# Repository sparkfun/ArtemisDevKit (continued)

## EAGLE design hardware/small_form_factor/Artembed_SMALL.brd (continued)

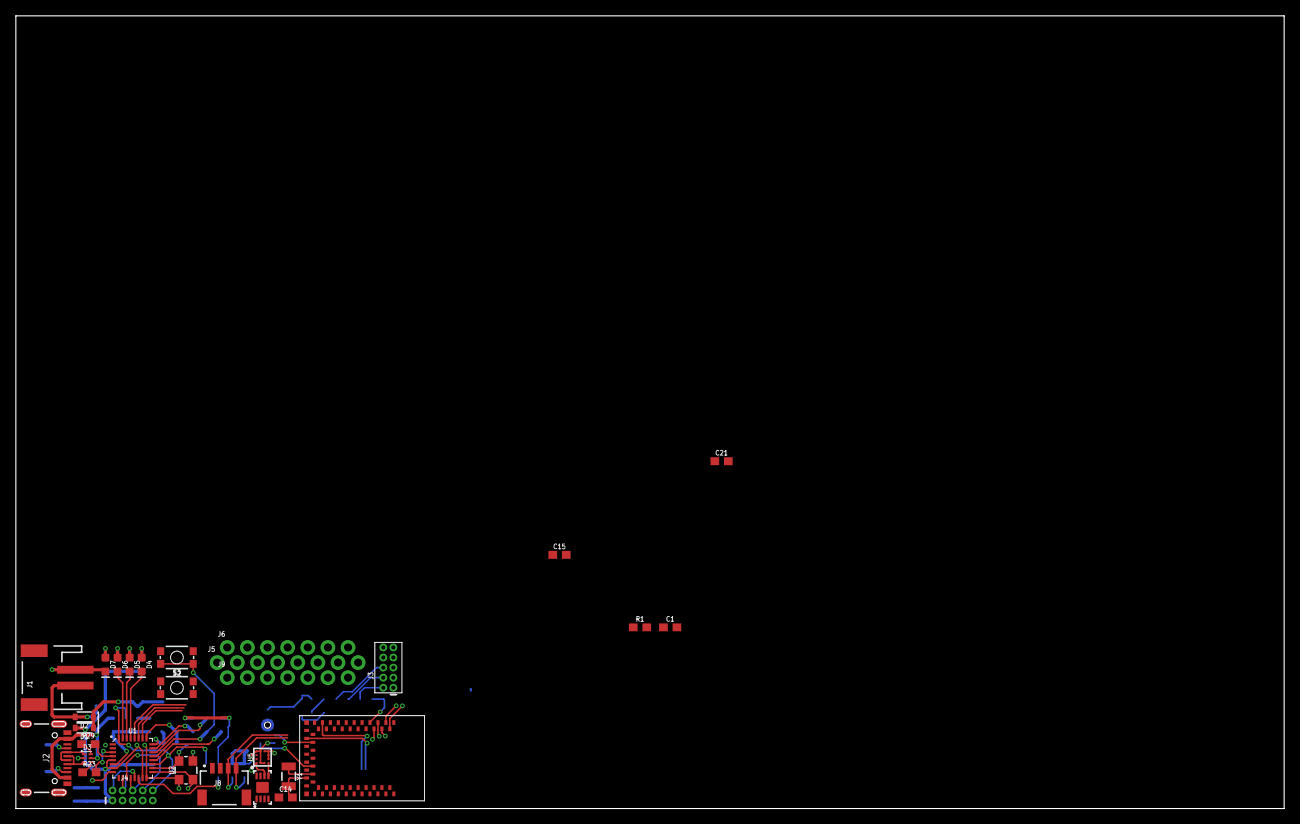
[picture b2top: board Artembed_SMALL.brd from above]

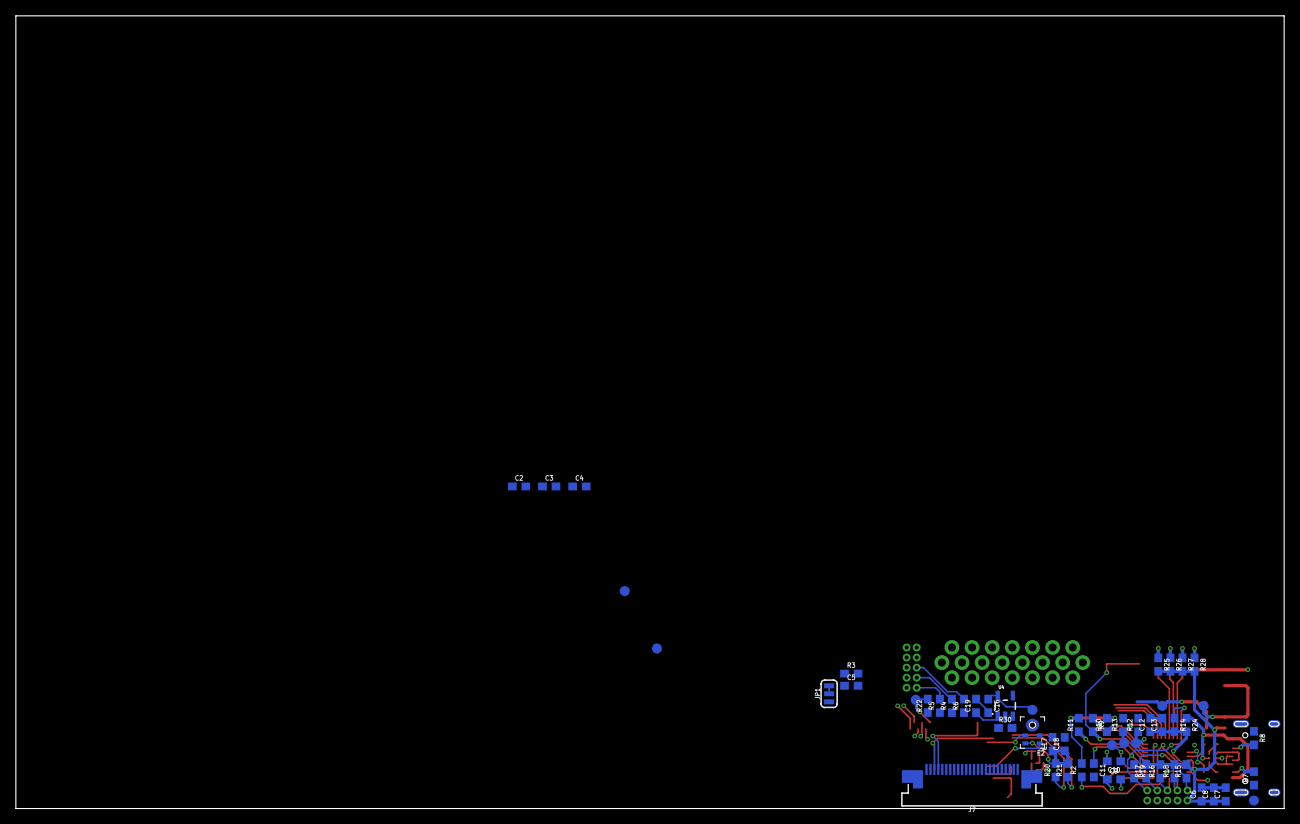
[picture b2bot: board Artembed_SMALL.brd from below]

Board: 2 copper layers, 160.0 x 100.0 mm, 88 parts (57 on the bottom side), 81 nets.

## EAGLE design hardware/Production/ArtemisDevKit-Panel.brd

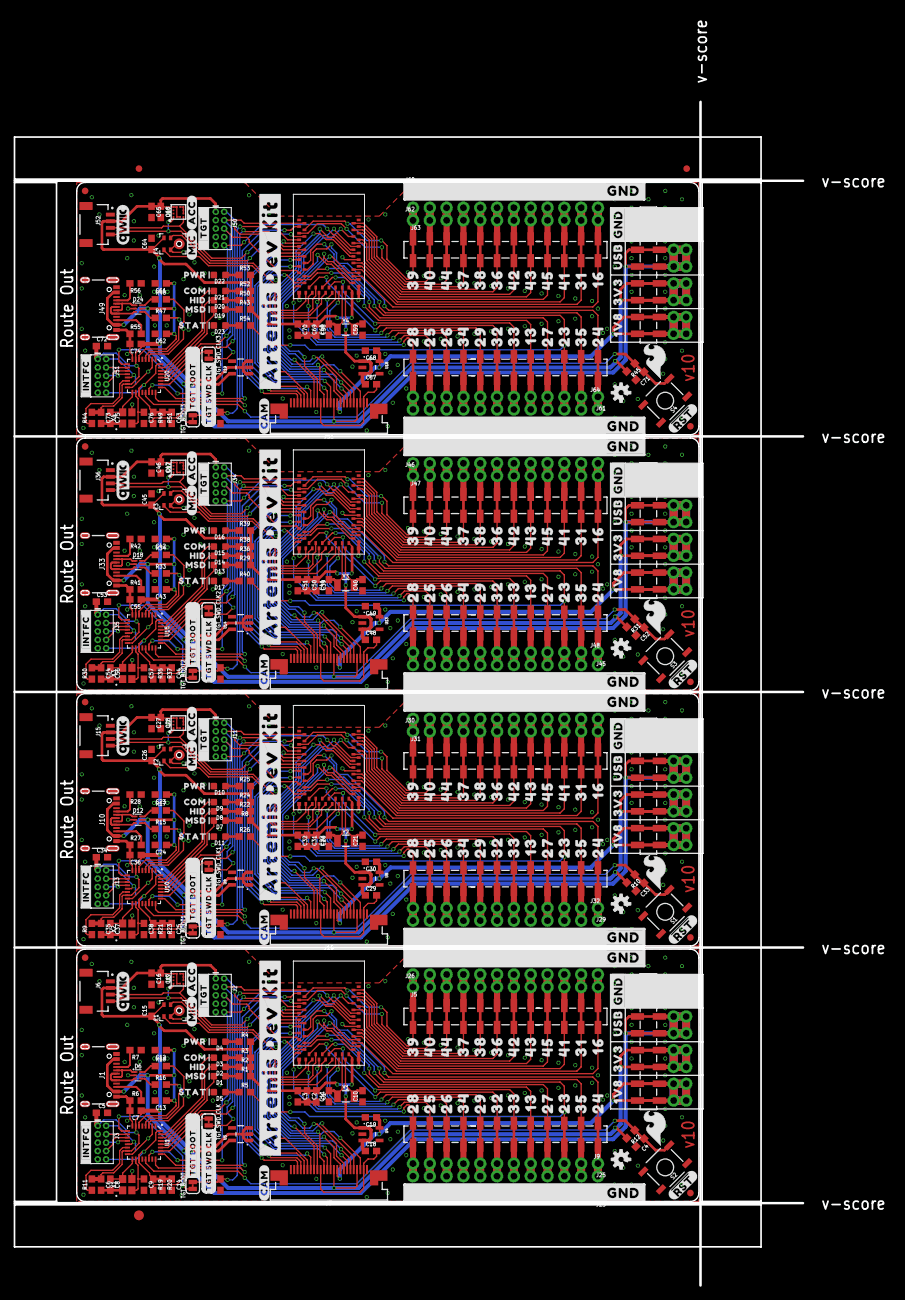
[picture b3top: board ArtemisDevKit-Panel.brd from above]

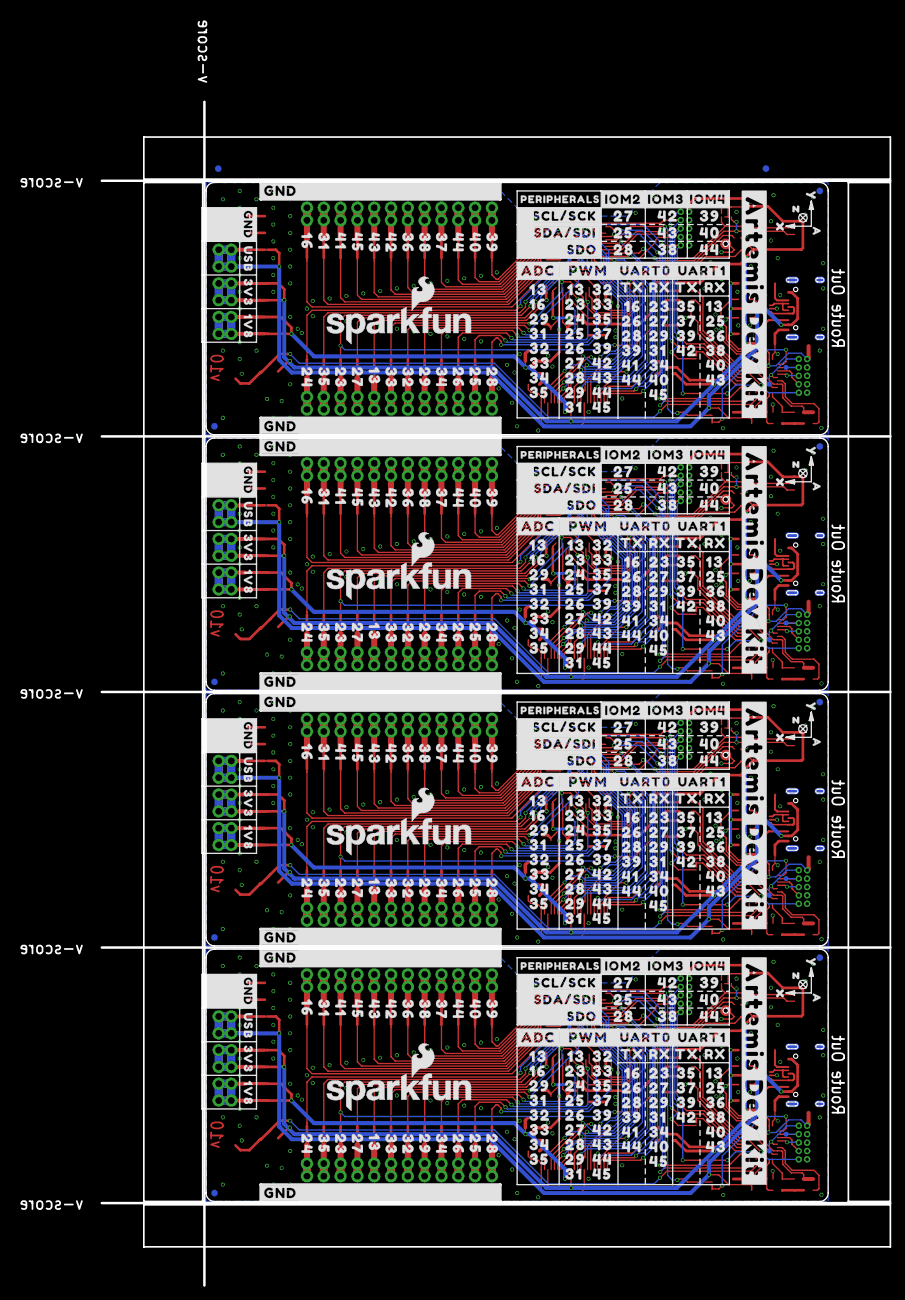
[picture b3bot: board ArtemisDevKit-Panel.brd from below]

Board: 2 copper layers, 119.1 x 178.8 mm, 917 parts (454 on the bottom side), 328 nets.

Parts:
C1, C17, C20, C28, C39, C47, C58, C66: 10uF; 0603
C2, C12, C15, C18, C19, C23, C26, C29, C30, C31, C42, C45, C48, C49, C50, C61, C64, C67, C68, C69: 1.0uF; 0603
C3, C4, C6, C7, C13, C14, C16, C24, C25, C27, C32, C33, C35, C36, C43, C44, C46, C51, C52, C54, C55, C62, C63, C65, C70, C71, C73, C74: 0.1uF; 0603
C5, C34, C53, C72: 2.2uF; 0603
C8, C9, C37, C38, C56, C57, C75, C76: 12pF; 0603
C10, C11, C21, C22, C40, C41, C59, C60: 15pF; 0603
D1, D5, D7, D11, D13, D17, D19, D23: BLUE; LED-0603
D2, D8, D14, D20: GREEN; LED-0603
D3, D9, D15, D21: Yellow; LED-0603
D4, D10, D16, D22: RED; LED-0603
D6, D12, D18, D24: PRTR5V0U2F; SOT886
E1, E2, E3, E4: SPH0641LM4H-1; SPH0641LM4H-1_MICROPHONE
E$1, E$2, E$3, E$4: FIDUCIAL-1X2
E$5: FIDUCIAL-1.5X3
FD1, FD2, FD3, FD4, FD5, FD6, FD7, FD8, FD9, FD10, FD11, FD12, FD13, FD14, FD15, FD16: FIDUCIAL1X2; FIDUCIAL-1X2
J1, J10, J33, J49: USB; USB-C-16P
J2, J11, J34, J50: CORTEX_JTAG_DEBUG_MINIMUM_PTH; 2X5-PTH-1.27MM
J3, J13, J35, J51: CORTEX_JTAG_DEBUG_PTH; 2X5-PTH-1.27MM
J4, J17, J38, J54: SMD; 1X08_SMD_COMBINED
J5, J9, J31, J32, J47, J48, J63, J64: 1X12_SMD_COMBINED
J6, J15, J36, J52: QWIIC_RIGHT_ANGLE; JST04_1MM_RA
J7, J16, J37, J53: CAMERA-HIMAXBOTTOM-CONTACT; FPC-24-AMPHENOL-SFV24R-1STE1HLF
J8, J12, J18, J19, J39, J40, J55, J56: PTH; 1X08_NO_SILK
J14, J20, J21, J22, J23, J24, J25, J26, J27, J28, J29, J30, J41, J42, J43, J44, J45, J46, J57, J58, J59, J60, J61, J62: PTH; 1X12_NO_SILK
LOGO1, LOGO3, LOGO5, LOGO7: OSHW-LOGOS; OSHW-LOGO-S
LOGO2, LOGO4, LOGO6, LOGO8: SFE_LOGO_NAME_FLAME.2_INCH; SFE_LOGO_NAME_FLAME_.2
R1, R2, R3, R4, R5, R8, R22, R24, R25, R26, R29, R36, R38, R39, R40, R43, R50, R52, R53, R54: 330; 0603
R6, R7, R27, R28, R41, R42, R55, R56: 5.1k; 0603
R9, R10, R11, R12, R13, R14, R20, R23, R30, R31, R32, R37, R44, R45, R46, R51: 10k; 0603
R15, R16, R17, R18, R33, R34, R47, R48: 33; 0603
R19, R21, R35, R49: 5.62k; 0603
S1, S2, S3, S4: TGT_RST; TACTILE_SWITCH_SMD_5.2MM
TGT_BOOT, TGT_BOOT1, TGT_BOOT2, TGT_BOOT3: JUMPER-SMT_2_NC_TRACE_SILK; SMT-JUMPER_2_NC_TRACE_SILK
TGT_SWD_CLK, TGT_SWD_CLK1, TGT_SWD_CLK2, TGT_SWD_CLK3: JUMPER-SMT_2_NC_TRACE_SILK; SMT-JUMPER_2_NC_TRACE_SILK
TP1, TP3, TP5, TP7: INTFC_SWDIO; PAD.03X.03
TP2, TP4, TP6, TP8: INTFC_SWDCLK; PAD.03X.03
U1, U10, U15, U20: DAPLINK_KL26Z128VFM4; QFN-32-NOPAD
U2, U6, U11, U16: ARTEMIS_MODULESMD; ARTEMIS_FP
U3, U7, U12, U17: LIS2DH12; LGA-12-LISDH12
U4, U8, U13, U18: AP2127K-1.8V; SOT23-5
U5, U9, U14, U19: 3.3V; SOT23-5
U$1, U$2, U$133, U$134, U$311, U$312, U$465, U$466: #GND#10
U$3, U$132, U$135, U$177, U$313, U$331, U$467, U$485: 15_#GND#
U$4, U$129, U$136, U$174, U$314, U$328, U$468, U$482: 16_1V8
U$5, U$130, U$139, U$175, U$315, U$329, U$469, U$483: 17_3V3
U$6, U$131, U$143, U$176, U$316, U$330, U$470, U$484: 18_USB
U$7, U$64, U$98, U$147, U$184, U$209, U$234, U$277, U$338, U$363, U$388, U$431, U$492, U$517, U$542, U$585: 33_16
U$8, U$73, U$97, U$149, U$154, U$185, U$211, U$224, U$243, U$276, U$339, U$365, U$378, U$397, U$430, U$493, U$519, U$532, U$551, U$584: 41_31
U$9, U$68, U$96, U$186, U$238, U$275, U$340, U$392, U$429, U$494, U$546, U$583: 51_41
U$10, U$55, U$76, U$163, U$187, U$233, U$246, U$274, U$341, U$387, U$400, U$428, U$495, U$541, U$554, U$582: 55_45
U$11, U$54, U$86, U$91, U$161, U$188, U$231, U$256, U$261, U$273, U$342, U$385, U$410, U$415, U$427, U$496, U$539, U$564, U$569, U$581: 53_43
U$12, U$53, U$80, U$90, U$160, U$189, U$230, U$250, U$260, U$272, U$343, U$384, U$404, U$414, U$426, U$497, U$538, U$558, U$568, U$580: 52_42
U$13, U$52, U$83, U$190, U$253, U$271, U$344, U$407, U$425, U$498, U$561, U$579: 46_36
U$14, U$51, U$84, U$92, U$191, U$254, U$262, U$270, U$345, U$408, U$416, U$424, U$499, U$562, U$570, U$578: 48_38
U$15, U$50, U$78, U$158, U$192, U$228, U$248, U$269, U$346, U$382, U$402, U$423, U$500, U$536, U$556, U$577: 47_37
U$16, U$49, U$69, U$95, U$162, U$193, U$232, U$239, U$265, U$268, U$347, U$386, U$393, U$419, U$422, U$501, U$540, U$547, U$573, U$576: 54_44
U$17, U$48, U$75, U$85, U$94, U$194, U$245, U$255, U$264, U$267, U$348, U$399, U$409, U$418, U$421, U$502, U$553, U$563, U$572, U$575: 50_40
U$18, U$47, U$67, U$79, U$93, U$159, U$195, U$229, U$237, U$249, U$263, U$266, U$349, U$383, U$391, U$403, U$417, U$420, U$503, U$537, U$545, U$557, U$571, U$574: 49_39
U$19, U$58, U$110, U$196, U$218, U$289, U$350, U$372, U$443, U$504, U$526, U$597: 35_24
U$20, U$77, U$109, U$153, U$157, U$197, U$215, U$227, U$247, U$288, U$351, U$369, U$381, U$401, U$442, U$505, U$523, U$535, U$555, U$596: 45_35
U$21, U$57, U$70, U$108, U$198, U$217, U$240, U$287, U$352, U$371, U$394, U$441, U$506, U$525, U$548, U$595: 34_23
U$22, U$61, U$71, U$87, U$107, U$199, U$221, U$241, U$257, U$286, U$353, U$375, U$395, U$411, U$440, U$507, U$529, U$549, U$565, U$594: 38_27
U$23, U$56, U$81, U$106, U$146, U$200, U$208, U$216, U$251, U$285, U$354, U$362, U$370, U$405, U$439, U$508, U$516, U$524, U$559, U$593: 32_13
U$24, U$105, U$151, U$156, U$201, U$213, U$226, U$284, U$355, U$367, U$380, U$438, U$509, U$521, U$534, U$592: 43_33
U$25, U$104, U$150, U$155, U$202, U$212, U$225, U$283, U$356, U$366, U$379, U$437, U$510, U$520, U$533, U$591: 42_32
U$26, U$63, U$72, U$103, U$148, U$203, U$210, U$223, U$242, U$282, U$357, U$364, U$377, U$396, U$436, U$511, U$518, U$531, U$550, U$590: 40_29
U$27, U$74, U$102, U$152, U$204, U$214, U$244, U$281, U$358, U$368, U$398, U$435, U$512, U$522, U$552, U$589: 44_34
U$28, U$60, U$65, U$101, U$205, U$220, U$235, U$280, U$359, U$374, U$389, U$434, U$513, U$528, U$543, U$588: 37_26
U$29, U$59, U$82, U$88, U$100, U$206, U$219, U$252, U$258, U$279, U$360, U$373, U$406, U$412, U$433, U$514, U$527, U$560, U$566, U$587: 36_25
U$30, U$62, U$66, U$89, U$99, U$207, U$222, U$236, U$259, U$278, U$361, U$376, U$390, U$413, U$432, U$515, U$530, U$544, U$567, U$586: 39_28
U$31, U$167, U$321, U$475: 19_#IOM2#
U$32, U$127, U$309, U$463: QWIIC_6MM
U$33, U$168, U$322, U$476: 20_#IOM3#
U$34, U$169, U$323, U$477: 21_#IOM4#
U$35, U$304, U$458, U$612: #TGT#3
U$36, U$303, U$457, U$611: #ARTEMIS_DEV_KIT#0
U$37, U$299, U$453, U$607: #SCL#SCK#23
U$38, U$170, U$324, U$478: 30_#PWM#
U$39, U$171, U$325, U$479: 29_#ADC#
U$40, U$172, U$326, U$480: 25_#UART0#
U$41, U$173, U$327, U$481: 26_#UART1#
U$42, U$43, U$144, U$164, U$317, U$318, U$471, U$472: 27_TX
U$44, U$46, U$165, U$166, U$319, U$320, U$473, U$474: 28_RX
U$45, U$128, U$310, U$464: SFE_LOGO_FLAME_.2
U$111, U$300, U$454, U$608: #SDA#SDI#24
U$112, U$301, U$455, U$609: #SDO#25
U$113, U$290, U$444, U$598: 14_A
U$114, U$291, U$445, U$599: 15_X
U$115, U$292, U$446, U$600: 16_Y
U$116, U$293, U$447, U$601: 17_Z
U$117, U$294, U$448, U$602: 7_COM
U$118, U$295, U$449, U$603: 8_HID
U$119, U$296, U$450, U$604: 9_MSD
U$120, U$297, U$451, U$605: 10_STAT
U$121, U$298, U$452, U$606: 6_PWR
U$122, U$302, U$456, U$610: #ARTEMIS_DEV_KIT#1
U$123, U$305, U$459, U$613: #INTFC#2
U$124, U$306, U$460, U$614: #TGT_BOOT#4
U$125, U$307, U$461, U$615: #TGT_SWD_CLK#5
U$126, U$308, U$462, U$616: #CAM#13
U$137, U$178, U$332, U$486: #MIC#11
U$138, U$179, U$333, U$487: #ACC#12
U$140, U$141, U$180, U$181, U$334, U$335, U$488, U$489: 14_#GND#
U$142, U$182, U$336, U$490: ##RST##18
U$145, U$183, U$337, U$491: 19_PERIPHERALS
X1, X2, X3, X4: 16MHz; CRYSTAL-SMD-2X2.5MM
Y1, Y2, Y3, Y4: 32.768kHz; CRYSTAL-SMD-3.2X1.5MM

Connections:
1.8V: C19.1, J4.7, J4.7@2, J4.8, J4.8@2, J7.10, J8.7, J8.8, J12.7, J12.8, U4.5
1.8V1: C30.1, J16.10, J17.7, J17.7@2, J17.8, J17.8@2, J18.7, J18.8, J19.7, J19.8, U8.5
1.8V2: C49.1, J37.10, J38.7, J38.7@2, J38.8, J38.8@2, J39.7, J39.8, J40.7, J40.8, U13.5
1.8V3: C68.1, J53.10, J54.7, J54.7@2, J54.8, J54.8@2, J55.7, J55.8, J56.7, J56.8, U18.5
3.3V: C1.1, C2.1, C3.1, C5.1, C6.1, C7.1, C15.1, C16.1, C17.1, C18.1, E1.5, J2.1, J3.1, J4.5, J4.5@2, J4.6, J4.6@2, J6.2, J7.4, J7.11, J8.5, J8.6, J12.5, J12.6, R1.2, R2.2, R3.2, R4.2, R11.2, R12.2, U1.7, U1.15, U2.VDD@36, U2.VDD@37, U3.2, U3.3, U3.9, U3.10, U4.1, U4.3, U5.5
3.3V1: C20.1, C26.1, C27.1, C28.1, C29.1, C31.1, C32.1, C34.1, C35.1, C36.1, E2.5, J11.1, J13.1, J15.2, J16.4, J16.11, J17.5, J17.5@2, J17.6, J17.6@2, J18.5, J18.6, J19.5, J19.6, R8.2, R9.2, R10.2, R22.2, R24.2, R25.2, U6.VDD@36, U6.VDD@37, U7.2, U7.3, U7.9, U7.10, U8.1, U8.3, U9.5, U10.7, U10.15
3.3V2: C39.1, C45.1, C46.1, C47.1, C48.1, C50.1, C51.1, C53.1, C54.1, C55.1, E3.5, J34.1, J35.1, J36.2, J37.4, J37.11, J38.5, J38.5@2, J38.6, J38.6@2, J39.5, J39.6, J40.5, J40.6, R29.2, R30.2, R31.2, R36.2, R38.2, R39.2, U11.VDD@36, U11.VDD@37, U12.2, U12.3, U12.9, U12.10, U13.1, U13.3, U14.5, U15.7, U15.15
3.3V3: C58.1, C64.1, C65.1, C66.1, C67.1, C69.1, C70.1, C72.1, C73.1, C74.1, E4.5, J50.1, J51.1, J52.2, J53.4, J53.11, J54.5, J54.5@2, J54.6, J54.6@2, J55.5, J55.6, J56.5, J56.6, R43.2, R44.2, R45.2, R50.2, R52.2, R53.2, U16.VDD@36, U16.VDD@37, U17.2, U17.3, U17.9, U17.10, U18.1, U18.3, U19.5, U20.7, U20.15
!INTFC_RST: C14.1, J3.10, R19.1, R20.1, U1.19, U1.32
!INTFC_RST1: C25.1, J13.10, R21.1, R23.1, U10.19, U10.32
!INTFC_RST2: C44.1, J35.10, R35.1, R37.1, U15.19, U15.32
!INTFC_RST3: C63.1, J51.10, R49.1, R51.1, U20.19, U20.32
!RST!_BTN: C4.1, R12.1, S2.3, U1.21
!RST!_BTN1: C33.1, R10.1, S1.3, U10.21
!RST!_BTN2: C52.1, R31.1, S3.3, U15.21
!RST!_BTN3: C71.1, R45.1, S4.3, U20.21
!TGT_RST: J2.10, U1.22, U2.~RST
!TGT_RST1: J11.10, U6.~RST, U10.22
!TGT_RST2: J34.10, U11.~RST, U15.22
!TGT_RST3: J50.10, U16.~RST, U20.22
CAMERA_D0: J7.14, U2.D0
CAMERA_D1: J7.3, U2.D1
CAMERA_D2: J7.9, U2.D2
CAMERA_D3: J7.5, U2.D3
CAMERA_D4: J7.12, U2.~D4
CAMERA_D5: J7.20, U2.~D5
CAMERA_D6: J7.19, U2.~D6
CAMERA_D7: J7.13, U2.D7
CAMERA_D8: J16.3, U6.D1
CAMERA_D9: J16.5, U6.D3
CAMERA_D10: J16.12, U6.~D4
CAMERA_D11: J16.20, U6.~D5
CAMERA_D12: J16.19, U6.~D6
CAMERA_D13: J16.13, U6.D7
CAMERA_D14: J16.14, U6.D0
CAMERA_D15: J16.9, U6.D2
CAMERA_D16: J37.3, U11.D1
CAMERA_D17: J37.5, U11.D3
CAMERA_D18: J37.12, U11.~D4
CAMERA_D19: J37.20, U11.~D5
CAMERA_D20: J37.19, U11.~D6
CAMERA_D21: J37.13, U11.D7
CAMERA_D22: J37.14, U11.D0
CAMERA_D23: J37.9, U11.D2
CAMERA_D24: J53.3, U16.D1
CAMERA_D25: J53.5, U16.D3
CAMERA_D26: J53.12, U16.~D4
CAMERA_D27: J53.20, U16.~D5
CAMERA_D28: J53.19, U16.~D6
CAMERA_D29: J53.13, U16.D7
CAMERA_D30: J53.14, U16.D0
CAMERA_D31: J53.9, U16.D2
CAMERA_HSYNC: J7.16, U2.D17
CAMERA_HSYNC1: J16.16, U6.D17
CAMERA_HSYNC2: J37.16, U11.D17
CAMERA_HSYNC3: J53.16, U16.D17
CAMERA_INT: J7.18, U2.D10
CAMERA_INT1: J16.18, U6.D10
CAMERA_INT2: J37.18, U11.D10
CAMERA_INT3: J53.18, U16.D10
CAMERA_MCLK: J7.8, U2.~D18
CAMERA_MCLK1: J16.8, U6.~D18
CAMERA_MCLK2: J37.8, U11.~D18
CAMERA_MCLK3: J53.8, U16.~D18
CAMERA_PCLK: J7.17, U2.~D19
CAMERA_PCLK1: J16.17, U6.~D19
CAMERA_PCLK2: J37.17, U11.~D19
CAMERA_PCLK3: J53.17, U16.~D19
CAMERA_TRIG: J7.7, U2.D14
CAMERA_TRIG1: J16.7, U6.D14
CAMERA_TRIG2: J37.7, U11.D14
CAMERA_TRIG3: J53.7, U16.D14
CAMERA_VSYNC: J7.6, U2.D15
CAMERA_VSYNC1: J16.6, U6.D15
CAMERA_VSYNC2: J37.6, U11.D15
CAMERA_VSYNC3: J53.6, U16.D15
D1: J21.3, J30.3, J31.3, J31.3@2, U6.~D44
D2: J21.2, J30.2, J31.2, J31.2@2, U6.D40
D3: J21.1, J30.1, J31.1, J31.1@2, U6.~D39
D4: J21.5, J30.5, J31.5, J31.5@2, U6.D38
D5: J21.8, J30.8, J31.8, J31.8@2, U6.~D43
D6: J21.7, J30.7, J31.7, J31.7@2, U6.~D42
D7: J21.10, J30.10, J31.10, J31.10@2, U6.D41
D8: J20.11, J29.11, J32.11, J32.11@2, U6.~D25
D9: J20.10, J29.10, J32.10, J32.10@2, U6.~D26
D10: J20.4, J29.4, J32.4, J32.4@2, U6.~D27
D11: J20.12, J29.12, J32.12, J32.12@2, U6.~D28
D12: J21.6, J30.6, J31.6, J31.6@2, U6.D36
D13: J9.5, J9.5@2, J14.5, J25.5, U2.~AD13
D14: J21.4, J30.4, J31.4, J31.4@2, U6.~D37
D15: J21.9, J30.9, J31.9, J31.9@2, U6.~D45
D16: J5.12, J5.12@2, J22.12, J26.12, U2.AD16
D17: J20.5, J29.5, J32.5, J32.5@2, U6.~AD13
D18: J21.12, J30.12, J31.12, J31.12@2, U6.AD16
D19: J20.8, J29.8, J32.8, J32.8@2, U6.~AD29
D20: J21.11, J30.11, J31.11, J31.11@2, U6.~AD31
D21: J20.7, J29.7, J32.7, J32.7@2, U6.~AD32
D22: J20.6, J29.6, J32.6, J32.6@2, U6.~AD33/SWO
D23: J20.9, J29.9, J32.9, J32.9@2, U6.AD34
D23_LED: J9.3, J9.3@2, J14.3, J25.3, R5.2, U2.~D23
D23_LED1: J20.3, J29.3, J32.3, J32.3@2, R26.2, U6.~D23
D23_LED2: J41.3, J45.3, J48.3, J48.3@2, R40.2, U11.~D23
D23_LED3: J57.3, J61.3, J64.3, J64.3@2, R54.2, U16.~D23
D24: J9.1, J9.1@2, J14.1, J25.1, U2.~D24
D25: J9.11, J9.11@2, J14.11, J25.11, U2.~D25
D26: J9.10, J9.10@2, J14.10, J25.10, U2.~D26
D27: J9.4, J9.4@2, J14.4, J25.4, U2.~D27
D28: J9.12, J9.12@2, J14.12, J25.12, U2.~D28
D29: J9.8, J9.8@2, J14.8, J25.8, U2.~AD29
D30: J20.1, J29.1, J32.1, J32.1@2, U6.~D24
D31: J5.11, J5.11@2, J22.11, J26.11, U2.~AD31
D32: J9.7, J9.7@2, J14.7, J25.7, U2.~AD32
D33: J9.6, J9.6@2, J14.6, J25.6, U2.~AD33/SWO
D34: J9.9, J9.9@2, J14.9, J25.9, U2.AD34
D35: J9.2, J9.2@2, J14.2, J25.2, U2.~AD35
D36: J5.6, J5.6@2, J22.6, J26.6, U2.D36
D37: J5.4, J5.4@2, J22.4, J26.4, U2.~D37
D38: J5.5, J5.5@2, J22.5, J26.5, U2.D38
D39: J5.1, J5.1@2, J22.1, J26.1, U2.~D39
D40: J5.2, J5.2@2, J22.2, J26.2, U2.D40
D41: J5.10, J5.10@2, J22.10, J26.10, U2.D41
D42: J5.7, J5.7@2, J22.7, J26.7, U2.~D42
D43: J5.8, J5.8@2, J22.8, J26.8, U2.~D43
D44: J5.3, J5.3@2, J22.3, J26.3, U2.~D44
D45: J5.9, J5.9@2, J22.9, J26.9, U2.~D45
D46: J20.2, J29.2, J32.2, J32.2@2, U6.~AD35
D47: J42.3, J46.3, J47.3, J47.3@2, U11.~D44
D48: J42.2, J46.2, J47.2, J47.2@2, U11.D40
D49: J42.1, J46.1, J47.1, J47.1@2, U11.~D39
D50: J42.5, J46.5, J47.5, J47.5@2, U11.D38
D51: J42.8, J46.8, J47.8, J47.8@2, U11.~D43
D52: J42.7, J46.7, J47.7, J47.7@2, U11.~D42
D53: J42.10, J46.10, J47.10, J47.10@2, U11.D41
D54: J41.11, J45.11, J48.11, J48.11@2, U11.~D25
D55: J41.10, J45.10, J48.10, J48.10@2, U11.~D26
D56: J41.4, J45.4, J48.4, J48.4@2, U11.~D27
D57: J41.12, J45.12, J48.12, J48.12@2, U11.~D28
D58: J42.6, J46.6, J47.6, J47.6@2, U11.D36
D59: J42.4, J46.4, J47.4, J47.4@2, U11.~D37
D60: J42.9, J46.9, J47.9, J47.9@2, U11.~D45
D61: J41.5, J45.5, J48.5, J48.5@2, U11.~AD13
D62: J42.12, J46.12, J47.12, J47.12@2, U11.AD16
D63: J41.8, J45.8, J48.8, J48.8@2, U11.~AD29
D64: J42.11, J46.11, J47.11, J47.11@2, U11.~AD31
D65: J41.7, J45.7, J48.7, J48.7@2, U11.~AD32
D66: J41.6, J45.6, J48.6, J48.6@2, U11.~AD33/SWO
D67: J41.9, J45.9, J48.9, J48.9@2, U11.AD34
D68: J41.1, J45.1, J48.1, J48.1@2, U11.~D24
D69: J41.2, J45.2, J48.2, J48.2@2, U11.~AD35
D70: J58.3, J62.3, J63.3, J63.3@2, U16.~D44
D71: J58.2, J62.2, J63.2, J63.2@2, U16.D40
D72: J58.1, J62.1, J63.1, J63.1@2, U16.~D39
D73: J58.5, J62.5, J63.5, J63.5@2, U16.D38
D74: J58.8, J62.8, J63.8, J63.8@2, U16.~D43
D75: J58.7, J62.7, J63.7, J63.7@2, U16.~D42
D76: J58.10, J62.10, J63.10, J63.10@2, U16.D41
D77: J57.11, J61.11, J64.11, J64.11@2, U16.~D25
D78: J57.10, J61.10, J64.10, J64.10@2, U16.~D26
D79: J57.4, J61.4, J64.4, J64.4@2, U16.~D27
D80: J57.12, J61.12, J64.12, J64.12@2, U16.~D28
D81: J58.6, J62.6, J63.6, J63.6@2, U16.D36
D82: J58.4, J62.4, J63.4, J63.4@2, U16.~D37
D83: J58.9, J62.9, J63.9, J63.9@2, U16.~D45
D84: J57.5, J61.5, J64.5, J64.5@2, U16.~AD13
D85: J58.12, J62.12, J63.12, J63.12@2, U16.AD16
D86: J57.8, J61.8, J64.8, J64.8@2, U16.~AD29
D87: J58.11, J62.11, J63.11, J63.11@2, U16.~AD31
D88: J57.7, J61.7, J64.7, J64.7@2, U16.~AD32
D89: J57.6, J61.6, J64.6, J64.6@2, U16.~AD33/SWO
D90: J57.9, J61.9, J64.9, J64.9@2, U16.AD34
D91: J57.1, J61.1, J64.1, J64.1@2, U16.~D24
D92: J57.2, J61.2, J64.2, J64.2@2, U16.~AD35
GND: C1.2, C2.2, C3.2, C4.2, C5.2, C6.2, C7.2, C8.2, C9.2, C10.1, C11.1, C12.2, C13.2, C14.2, C15.2, C16.2, C17.2, C18.2, C19.2, D4.C, D5.C, D6.2, E1.2, E1.3, E1.6, E1.7, E1.8, J1.GND, J1.GND2, J2.3, J2.5, J2.9, J3.3, J3.5, J3.9, J4.1, J4.1@2, J4.2, J4.2@2, J6.1, J7.2, J7.15, J8.1, J8.2, J12.1, J12.2, J23.1, J23.2, J23.3, J23.4, J23.5, J23.6, J23.7, J23.8, J23.9, J23.10, J23.11, J23.12, J24.1, J24.2, J24.3, J24.4, J24.5, J24.6, J24.7, J24.8, J24.9, J24.10, J24.11, J24.12, R6.1, R7.1, R13.1, R20.2, S2.1, U1.2, U1.8, U1.16, U2.GND@1, U2.GND@22, U2.GND@38, U2.GND@39, U2.GND@47, U2.GND@59, U3.5, U3.6, U3.7, U3.8, U4.2, U5.2, X1.P2, X1.P4
GND1: C20.2, C21.1, C22.1, C23.2, C24.2, C25.2, C26.2, C27.2, C28.2, C29.2, C30.2, C31.2, C32.2, C33.2, C34.2, C35.2, C36.2, C37.2, C38.2, D10.C, D11.C, D12.2, E2.2, E2.3, E2.6, E2.7, E2.8, J10.GND, J10.GND2, J11.3, J11.5, J11.9, J13.3, J13.5, J13.9, J15.1, J16.2, J16.15, J17.1, J17.1@2, J17.2, J17.2@2, J18.1, J18.2, J19.1, J19.2, J27.1, J27.2, J27.3, J27.4, J27.5, J27.6, J27.7, J27.8, J27.9, J27.10, J27.11, J27.12, J28.1, J28.2, J28.3, J28.4, J28.5, J28.6, J28.7, J28.8, J28.9, J28.10, J28.11, J28.12, R14.1, R23.2, R27.1, R28.1, S1.1, U6.GND@1, U6.GND@22, U6.GND@38, U6.GND@39, U6.GND@47, U6.GND@59, U7.5, U7.6, U7.7, U7.8, U8.2, U9.2, U10.2, U10.8, U10.16, X2.P2, X2.P4
GND2: C39.2, C40.1, C41.1, C42.2, C43.2, C44.2, C45.2, C46.2, C47.2, C48.2, C49.2, C50.2, C51.2, C52.2, C53.2, C54.2, C55.2, C56.2, C57.2, D16.C, D17.C, D18.2, E3.2, E3.3, E3.6, E3.7, E3.8, J33.GND, J33.GND2, J34.3, J34.5, J34.9, J35.3, J35.5, J35.9, J36.1, J37.2, J37.15, J38.1, J38.1@2, J38.2, J38.2@2, J39.1, J39.2, J40.1, J40.2, J43.1, J43.2, J43.3, J43.4, J43.5, J43.6, J43.7, J43.8, J43.9, J43.10, J43.11, J43.12, J44.1, J44.2, J44.3, J44.4, J44.5, J44.6, J44.7, J44.8, J44.9, J44.10, J44.11, J44.12, R32.1, R37.2, R41.1, R42.1, S3.1, U11.GND@1, U11.GND@22, U11.GND@38, U11.GND@39, U11.GND@47, U11.GND@59, U12.5, U12.6, U12.7, U12.8, U13.2, U14.2, U15.2, U15.8, U15.16, X3.P2, X3.P4
GND3: C58.2, C59.1, C60.1, C61.2, C62.2, C63.2, C64.2, C65.2, C66.2, C67.2, C68.2, C69.2, C70.2, C71.2, C72.2, C73.2, C74.2, C75.2, C76.2, D22.C, D23.C, D24.2, E4.2, E4.3, E4.6, E4.7, E4.8, J49.GND, J49.GND2, J50.3, J50.5, J50.9, J51.3, J51.5, J51.9, J52.1, J53.2, J53.15, J54.1, J54.1@2, J54.2, J54.2@2, J55.1, J55.2, J56.1, J56.2, J59.1, J59.2, J59.3, J59.4, J59.5, J59.6, J59.7, J59.8, J59.9, J59.10, J59.11, J59.12, J60.1, J60.2, J60.3, J60.4, J60.5, J60.6, J60.7, J60.8, J60.9, J60.10, J60.11, J60.12, R46.1, R51.2, R55.1, R56.1, S4.1, U16.GND@1, U16.GND@22, U16.GND@38, U16.GND@39, U16.GND@47, U16.GND@59, U17.5, U17.6, U17.7, U17.8, U18.2, U19.2, U20.2, U20.8, U20.16, X4.P2, X4.P4
INTFC_NC1: J13.6, U10.12
INTFC_NC2: J13.8, U10.11
INTFC_NC3: J35.6, U15.12
INTFC_NC4: J35.8, U15.11
INTFC_NC5: J3.8, U1.11
INTFC_NC6: J3.6, U1.12
INTFC_NC7: J51.6, U20.12
INTFC_NC8: J51.8, U20.11
INTFC_SWDCLK: J3.4, TP2.P$1, U1.10
INTFC_SWDCLK1: J13.4, TP4.P$1, U10.10
INTFC_SWDCLK2: J35.4, TP6.P$1, U15.10
INTFC_SWDCLK3: J51.4, TP8.P$1, U20.10
INTFC_SWDIO: J3.2, TP1.P$1, U1.13
INTFC_SWDIO1: J13.2, TP3.P$1, U10.13
INTFC_SWDIO2: J35.2, TP5.P$1, U15.13
INTFC_SWDIO3: J51.2, TP7.P$1, U20.13
LED_HID: D2.C, U1.30
LED_HID1: D8.C, U10.30
LED_HID2: D14.C, U15.30
LED_HID3: D20.C, U20.30
LED_MSD: D1.C, U1.29
LED_MSD1: D7.C, U10.29
LED_MSD2: D13.C, U15.29
LED_MSD3: D19.C, U20.29
LED_UART: D3.C, U1.31
LED_UART1: D9.C, U10.31
LED_UART2: D15.C, U15.31
LED_UART3: D21.C, U20.31
unnamed: D1.A, R1.1
unnamed: D2.A, R2.1
unnamed: D3.A, R3.1
unnamed: J1.B5, R6.2
unnamed: J1.A5, R7.2
unnamed: D5.A, R5.1
unnamed: D4.A, R4.1
unnamed: D6.4, R16.1
unnamed: D6.6, R18.1
unnamed: R11.1, U1.14
unnamed: J10.B5, R27.2
unnamed: TGT_SWD_CLK.1, U1.26
unnamed: C8.1, U1.17, X1.P1
unnamed: C10.2, U2.XI, Y1.P$2
unnamed: C11.2, U2.XO, Y1.P$1
unnamed: C9.1, U1.18, X1.P3
unnamed: J10.A5, R28.2
unnamed: TGT_BOOT.1, U1.9
unnamed: R9.1, U10.14
unnamed: C37.1, U10.17, X2.P1
unnamed: C38.1, U10.18, X2.P3
unnamed: C21.2, U6.XI, Y2.P$2
unnamed: C22.2, U6.XO, Y2.P$1
unnamed: D7.A, R8.1
unnamed: D8.A, R22.1
unnamed: D9.A, R24.1
unnamed: D10.A, R25.1
unnamed: D12.4, R15.1
unnamed: D12.6, R17.1
unnamed: D11.A, R26.1
unnamed: TGT_SWD_CLK1.1, U10.26
unnamed: TGT_BOOT1.1, U10.9
unnamed: J33.B5, R41.2
unnamed: J33.A5, R42.2
unnamed: R30.1, U15.14
unnamed: C56.1, U15.17, X3.P1
unnamed: C57.1, U15.18, X3.P3
unnamed: C40.2, U11.XI, Y3.P$2
unnamed: C41.2, U11.XO, Y3.P$1
unnamed: D13.A, R29.1
unnamed: D14.A, R36.1
unnamed: D15.A, R38.1
unnamed: D16.A, R39.1
unnamed: D18.4, R33.1
unnamed: D18.6, R34.1
unnamed: D17.A, R40.1
unnamed: TGT_SWD_CLK2.1, U15.26
unnamed: TGT_BOOT2.1, U15.9
unnamed: J49.B5, R55.2
unnamed: J49.A5, R56.2
unnamed: R44.1, U20.14
unnamed: C75.1, U20.17, X4.P1
unnamed: C76.1, U20.18, X4.P3
unnamed: C59.2, U16.XI, Y4.P$2
unnamed: C60.2, U16.XO, Y4.P$1
unnamed: D19.A, R43.1
unnamed: D20.A, R50.1
unnamed: D21.A, R52.1
unnamed: D22.A, R53.1
unnamed: D24.4, R47.1
unnamed: D24.6, R48.1
unnamed: D23.A, R54.1
unnamed: TGT_SWD_CLK3.1, U20.26
unnamed: TGT_BOOT3.1, U20.9
PDM_CLK: E1.4, U2.~AD12
PDM_CLK1: E2.4, U6.~AD12
PDM_CLK2: E3.4, U11.~AD12
PDM_CLK3: E4.4, U16.~AD12
PDM_DATA: E1.1, U2.~AD11
PDM_DATA1: E2.1, U6.~AD11
PDM_DATA2: E3.1, U11.~AD11
PDM_DATA3: E4.1, U16.~AD11
SCL: J6.4, J7.21, U2.D8, U3.1
SCL1: J15.4, J16.21, U6.D8, U7.1
SCL2: J36.4, J37.21, U11.D8, U12.1
SCL3: J52.4, J53.21, U16.D8, U17.1
SDA: J6.3, J7.22, U2.D9, U3.4
SDA1: J15.3, J16.22, U6.D9, U7.4
SDA2: J36.3, J37.22, U11.D9, U12.4
SDA3: J52.3, J53.22, U16.D9, U17.4
TGT_BOOT: R13.2, TGT_BOOT.2, U2.BOOT
TGT_BOOT1: R14.2, TGT_BOOT1.2, U6.BOOT
TGT_BOOT2: R32.2, TGT_BOOT2.2, U11.BOOT
TGT_BOOT3: R46.2, TGT_BOOT3.2, U16.BOOT
TGT_RX: U1.25, U2.RXI-0
TGT_RX1: U6.RXI-0, U10.25
TGT_RX2: U11.RXI-0, U15.25
TGT_RX3: U16.RXI-0, U20.25
TGT_SWCLK: J2.4, TGT_SWD_CLK.2, U2.SWDCK
TGT_SWCLK1: J11.4, TGT_SWD_CLK1.2, U6.SWDCK
TGT_SWCLK2: J34.4, TGT_SWD_CLK2.2, U11.SWDCK
TGT_SWCLK3: J50.4, TGT_SWD_CLK3.2, U16.SWDCK
TGT_SWDIO: J2.2, U1.27, U2.SWDIO
TGT_SWDIO1: J11.2, U6.SWDIO, U10.27
TGT_SWDIO2: J34.2, U11.SWDIO, U15.27
TGT_SWDIO3: J50.2, U16.SWDIO, U20.27
TGT_SWO: J2.6, U1.28, U2.~D22
TGT_SWO1: J11.6, U6.~D22, U10.28
TGT_SWO2: J34.6, U11.~D22, U15.28
TGT_SWO3: J50.6, U16.~D22, U20.28
TGT_TX: U1.24, U2.TXO-0
TGT_TX1: U6.TXO-0, U10.24
TGT_TX2: U11.TXO-0, U15.24
TGT_TX3: U16.TXO-0, U20.24
USB_D+_P: R16.2, U1.3
USB_D+_P1: R15.2, U10.3
USB_D+_P2: R33.2, U15.3
USB_D+_P3: R47.2, U20.3
USB_D+_R: D6.3, J1.A6, J1.B6
USB_D+_R1: D12.3, J10.A6, J10.B6
USB_D+_R2: D18.3, J33.A6, J33.B6
USB_D+_R3: D24.3, J49.A6, J49.B6
USB_D-_P: R18.2, U1.4
USB_D-_P1: R17.2, U10.4
USB_D-_P2: R34.2, U15.4
USB_D-_P3: R48.2, U20.4
USB_D-_R: D6.1, J1.A7, J1.B7
USB_D-_R1: D12.1, J10.A7, J10.B7
USB_D-_R2: D18.1, J33.A7, J33.B7
USB_D-_R3: D24.1, J49.A7, J49.B7
V_USB: C12.1, C13.1, D6.5, J1.VBUS1, J1.VBUS2, J4.3, J4.3@2, J4.4, J4.4@2, J8.3, J8.4, J12.3, J12.4, R19.2, U1.6, U5.1, U5.3
V_USB1: C23.1, C24.1, D12.5, J10.VBUS1, J10.VBUS2, J17.3, J17.3@2, J17.4, J17.4@2, J18.3, J18.4, J19.3, J19.4, R21.2, U9.1, U9.3, U10.6
V_USB2: C42.1, C43.1, D18.5, J33.VBUS1, J33.VBUS2, J38.3, J38.3@2, J38.4, J38.4@2, J39.3, J39.4, J40.3, J40.4, R35.2, U14.1, U14.3, U15.6
V_USB3: C61.1, C62.1, D24.5, J49.VBUS1, J49.VBUS2, J54.3, J54.3@2, J54.4, J54.4@2, J55.3, J55.4, J56.3, J56.4, R49.2, U19.1, U19.3, U20.6
